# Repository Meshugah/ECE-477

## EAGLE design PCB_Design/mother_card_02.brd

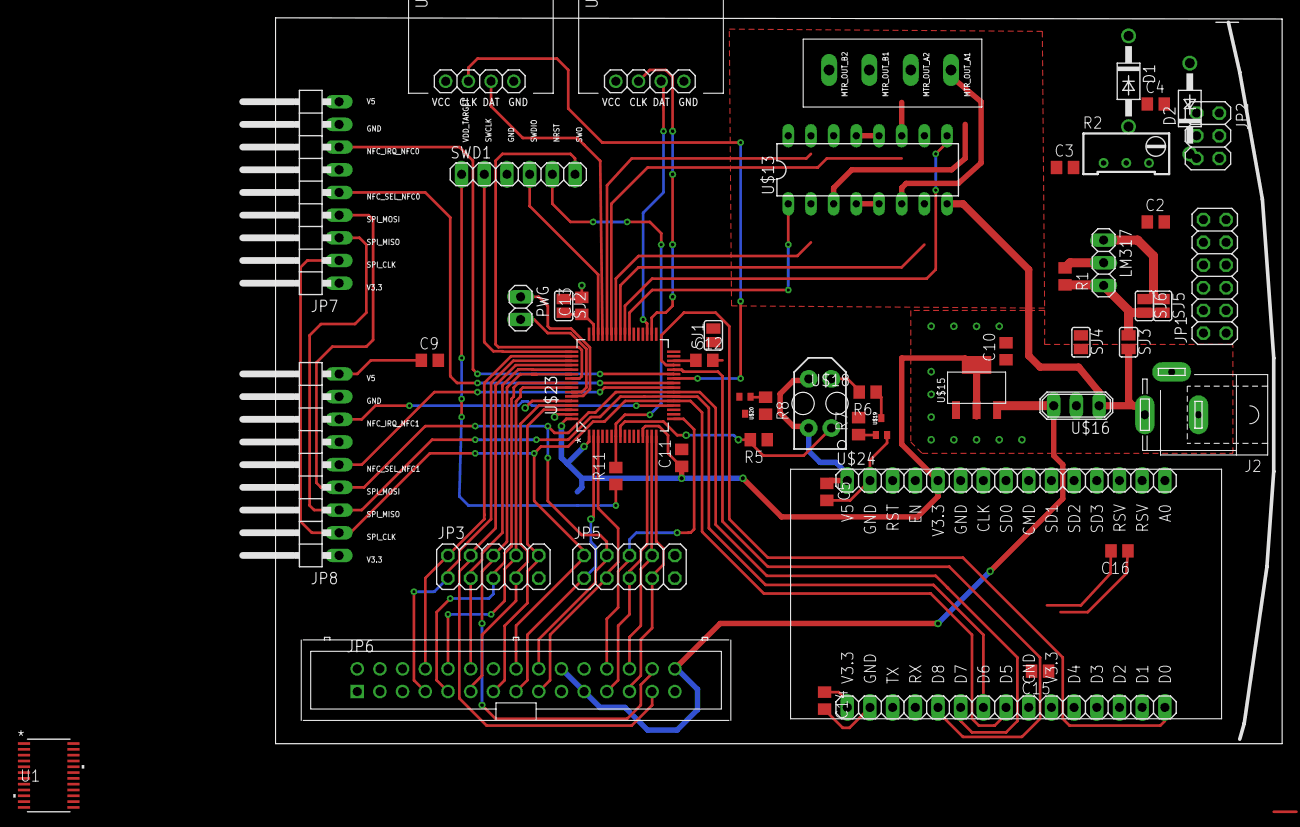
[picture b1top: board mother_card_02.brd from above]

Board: 2 copper layers, 112.7 x 81.3 mm, 51 parts (1 on the bottom side), 69 nets.

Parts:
C2, C4: 1u; C0805
C3: 0.1u; C0805
C5, C11, C12, C13, C14, C15, C16: C0805
C9, C10: 4.7u; C0805
D1, D2: 1N4004; DO41-10
J2: SPC4077
JP1: 2X06
JP2: 2X03
JP3, JP5: 2X05
JP6: 2X15/SOCK
JP7, JP8: 1X09/90
LM317: 1X03
PWG: 1X02
R1, R5, R6, R7, R8, R11: R0805
R2: RTRIM64W
SJ1, SJ2, SJ3, SJ4, SJ5, SJ6, SJ7: SJ
SWD1: 1X06
U1: 74LVC4245APWSOT355-1-L; SOT355-1-L
U$13: L293; DIL16
U$14: TERMINAL_BLOCK; 1X4/BLOCK
U$15: AP2114H
U$16: OKI-78SR-W36; SIP3
U$18: TCRT5000
U$19, U$20: DMG1012; SOT323
U$21, U$22: HX711
U$23: STM32F410RBT6; QFP50P1200X1200X160-64N
U$24: ESP8266

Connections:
F_A0: JP3.8, JP6.10, U$23.57
F_CLK: JP3.3, JP6.12, U$23.53
F_CS_DP: JP5.3, JP6.17, U$23.3
F_NCS1: JP3.5, JP6.9, U$23.56
F_NCS2: JP3.7, JP6.11, U$23.61
F_NRD: JP3.1, JP6.7, U$23.51
F_NRST: JP3.2, JP6.8, U$23.50
F_NWR: JP3.10, JP6.13, U$23.62
F_PWR_LED_B: JP3.4, JP6.27, U$23.52
F_PWR_LED_G: JP5.7, JP6.25, U$23.16
F_PWR_LED_R: JP5.5, JP6.23, U$23.14
F_RCLK: JP5.1, JP6.15, U$23.2
F_ROTA: JP6.2, U$23.9
F_ROTB: JP6.4, U$23.10
F_ROTSW: JP6.1, U$23.11
F_WIFI_LED_B: JP5.6, JP6.24, U$23.17
F_WIFI_LED_G: JP5.8, JP6.26, U$23.15
F_WIFI_LED_R: JP3.6, JP6.28, U$23.54
GND: C2.2, C5.2, C9.2, C10.2, C11.2, C12.2, C13.2, C14.2, C15.2, C16.2, J2.1, J2.2, JP3.9, JP6.6, JP6.19, JP6.22, JP7.8, JP8.8, R5.1, R7.2, R8.2, SJ1.1, SJ1.2, SJ2.1, SJ4.2, SWD1.3, U1.2, U1.11, U1.12, U1.13, U1.22, U$13.4, U$13.5, U$13.12, U$13.13, U$15.GND, U$16.GND, U$19.S, U$21.GND, U$22.GND, U$23.12, U$23.31, U$23.63, U$24.GND, U$24.GND@1, U$24.GND@2, U$24.GND@3
IR_SENS_ANLG_IN: R5.2, U$18.E, U$23.8
IR_START0: R7.1, U$19.G, U$23.38
IR_START1: R8.1, U$20.G, U$23.37
MTR_A1: U1.21, U$23.41
MTR_A2: U1.20, U$23.42
MTR_B1: U1.19, U$23.43
MTR_B2: U1.18, U$23.44
MTR_EN1,2: U$13.1, U$23.39
MTR_EN3,4: U$13.9, U$23.40
MTR_IN_A1: U1.3, U$13.7, U$14.P$4
MTR_IN_A2: U1.4, U$13.2
MTR_IN_B1: U1.5, U$13.10
MTR_IN_B2: U1.6, U$13.15
MTR_OUT_A2: U$13.3, U$14.P$3
MTR_OUT_B1: U$13.11, U$14.P$2
MTR_OUT_B2: U$13.14, U$14.P$1
unnamed: C12.1, U$23.30
unnamed: R6.2, U$18.CATH
unnamed: R6.1, U$19.D
NFC_IRQ_NFC0: JP7.7, U$23.27
NFC_IRQ_NFC1: JP8.7, U$23.20
NFC_SEL_NFC0: JP7.5, U$23.25
NFC_SEL_NFC1: JP8.5, U$23.24
NRST: R11.2, SWD1.5, U$23.7
PRG_RX<: PWG.1, U$23.59
PRG_TX>: PWG.2, U$23.58
SPI2_CLK: U$22.CLK, U$23.34
SPI2_MISO: U$22.DAT, U$23.35
SPI5_CLK: U$21.CLK, U$23.26
SPI5_MISO: U$21.DAT, U$23.45
SPI_CLK: JP5.2, JP6.16, JP7.2, JP8.2, U$23.21, U$24.D5
SPI_MISO: JP7.3, JP8.3, U$23.22, U$24.D6
SPI_MOSI: JP5.4, JP6.18, JP7.4, JP8.4, U$23.23, U$24.D7
SWCLK: SWD1.2, U$23.49
SWDIO: SWD1.4, U$23.46
SWO: SWD1.6, U$23.55
USB12V: D1.A, D2.C, LM317.3, R1.2, SJ3.1, SJ5.2, SJ6.2
USBGND: C3.2, C4.2, JP1.5, JP1.6, JP1.10, JP2.1, JP2.3, JP2.5, R2.1, SJ4.1
USBVBUS: C3.1, D1.C, LM317.1, SJ5.1, SJ6.1
V3.3: C10.1, C11.1, C14.1, C15.1, C16.1, JP6.5, JP6.14, JP7.1, JP8.1, SJ7.2, U1.23, U1.24, U$15.VOUT, U$15.VOUTB, U$21.VCC, U$22.VCC, U$23.1, U$23.13, U$23.32, U$23.48, U$23.64, U$24.V3.3, U$24.V3.3@1, U$24.V3.3@2
V5: C5.1, C9.1, JP6.20, JP6.21, JP6.30, JP7.9, JP8.9, U1.1, U$13.16, U$15.VIN, U$16.VO, U$18.A, U$18.COLL, U$24.V5
V12: C2.1, J2.3, SJ3.2, U$13.8, U$16.VI
VADJ: C4.1, D2.A, LM317.2, R1.1, R2.2
VBUS: JP2.2, JP2.4
VCAP_2: C13.1, SJ2.2, U$23.47
VCONN: JP1.1, JP2.6
VDD: JP1.3, JP1.12
VDD_TARGET: R11.1, SJ7.1, SWD1.1
WIFI_CS: U$23.28, U$24.D8
WIFI_IRQ: U$23.29, U$24.D0
